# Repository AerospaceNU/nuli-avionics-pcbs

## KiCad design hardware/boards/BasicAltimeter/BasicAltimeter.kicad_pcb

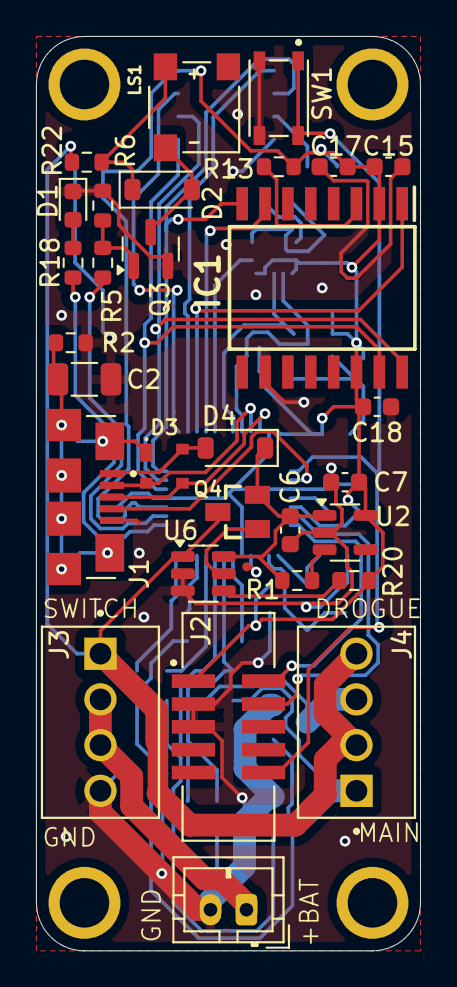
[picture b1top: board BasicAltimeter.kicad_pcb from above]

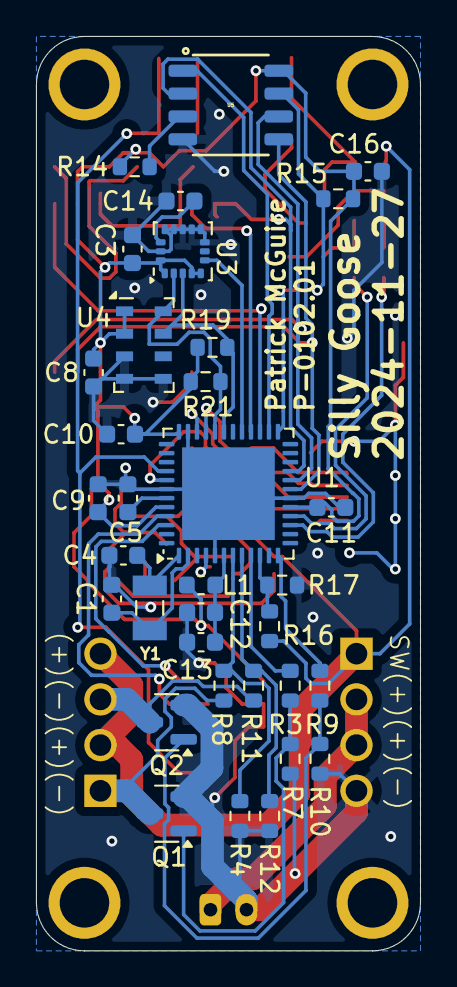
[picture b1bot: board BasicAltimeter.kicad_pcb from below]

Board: 2 copper layers, 21.3 x 50.8 mm, 69 parts (34 on the bottom side), 49 nets.

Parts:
C1, C4: 22pF; C_0603_1608Metric
C2: 4.7nF; C_1206_3216Metric
C3, C5, C8, C10, C11, C13, C14, C15, C18: 0.1uF; C_0603_1608Metric
C6, C7, C16: 10uF; C_0603_1608Metric
C9, C17: 1uF; C_0603_1608Metric
C12: 4.7uF; C_0603_1608Metric
D1: LED; LED_0603_1608Metric
D2, D4: D_Schottky; D_SOD-123
D3: PRTR5V0U2X_215; SOT143B
H1, H2, H3, H4: MountingHole; FixedMountingHole_2.5mm_Pad
IC1: S25FL512SAGMFV010; SOIC127P1030X265-16N
J1: ZX62-AB-5PA_31_; HIROSE_ZX62-AB-5PA_31_
J2: 20021521-00010T1LF; AMPHENOL_20021521-00010T1LF
J3, J4: Conn_01x04; TE_282834-4
J5: Conn_01x02; JST_PH_B2B-PH-K_1x02_P2.00mm_Vertical
L1: BLM18PG471SN1D; L_0603_1608Metric
LS1: CMT-0525-75-SMT-TR; XDCR_CMT-0525-75-SMT-TR
Q1, Q2, Q3: IRLML6244; SOT-23
Q4: FDN306P; SSOT-3
R1, R13: 100k; R_0603_1608Metric
R2, R20: 1M; R_0603_1608Metric
R3, R5, R9: 2k; R_0603_1608Metric
R4, R6, R7, R8, R10, R11, R12, R14, R15, R16, R17, R19, R21: 10k; R_0603_1608Metric
R18: 270; R_0603_1608Metric
R22: 50; R_0603_1608Metric
SW1: PTS810_SJM_250_SMTR_LFS; SW_PTS810_SJM_250_SMTR_LFS
TP12: TestPoint; TestPoint_Pad_D0.5mm
U1: ATSAMD21G18A-M; QFN-48-1EP_7x7mm_P0.5mm_EP5.15x5.15mm
U2: AP2112K-3.3; SOT-23-5
U3: ICM-20602; LGA-16_3x3mm_P0.5mm_LayoutBorder3x5y
U4: MS5607-02BA; LGA-8_3x5mm_P1.25mm
U5: MB85RS64V; SOIC127P600X155-8_R159_68_374R15
U6: LTC4412xS6; TSOT-23-6
Y1: ABS07-32.768KHZ-T; XTAL_ABS07-32.768KHZ-T

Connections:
+3.3V: C3.2, C5.2, C7.1, C8.2, C10.2, C11.2, C15.1, C16.2, C17.1, C18.2, IC1.2 (VCC), IC1.14 (VIO/RFU), J2.1, L1.1, R13.2, R14.1, R15.1, R19.1, R20.2, R21.1, U1.17 (VDDIO), U1.36 (VDDIO), U1.44 (VDDIN), U2.5 (VOUT), U3.1 (VDDIO), U3.4 (SAO/SD0), U3.5 (~CS), U3.16 (VDD), U4.1 (VDD), U4.2 (PS), U5.8 (VCC)
+BATT: J3.1, J4.2, J4.4, Q4.3, R16.1, R22.2, U6.1 (VIN)
/Connectors/D+: D3.3, J1.3 (D+), U1.34 (PA25)
/Connectors/D-: D3.2, J1.2 (D-), U1.33 (PA24)
/Connectors/DROGUE_CHANNEL: J4.3, Q2.3 (D), R11.2
/Connectors/MAIN_CHANNEL: J4.1, Q1.3 (D), R8.2
/Connectors/RESET: J2.10, SW1.1, SW1.2, U1.40 (~RESET)
/Connectors/SWCLK: J2.4, U1.45 (PA30)
/Connectors/SWDIO: J2.2, U1.46 (PA31)
/Connectors/USB_HOST: J1.4 (ID), U1.41 (PA28)
/Connectors/VUSB: D3.4, D4.2 (A), J1.1 (VCC)
/MCU/A1: R4.2, R8.1, U1.7 (PB08)
/MCU/A2: R11.1, R12.2, U1.8 (PB09)
/MCU/A3: R3.1, U1.9 (PA04)
/MCU/A4: R16.2, R17.1, U1.10 (PA05)
/MCU/AREF: TP12.1, U1.4 (PA03)
/MCU/D0_RX: R5.1, U1.16 (PA11)
/MCU/D1_TX: R18.1, U1.15 (PA10)
/MCU/D6: U1.29 (PA20), U3.6 (INT)
/MCU/D9: R9.1, U1.12 (PA07)
/MCU/D10: IC1.1 (HOLD#/IO3), U1.27 (PA18)
/MCU/D11: R15.2, U1.25 (PA16), U5.7 (~HOLD)
/MCU/D12: IC1.7 (CS#), U1.28 (PA19)
/MCU/D13: U1.26 (PA17), U5.1 (~CS)
/MCU/MISO: IC1.8 (SO/IO1), U1.21 (PA12), U5.2 (MISO)
/MCU/MOSI: IC1.15 (SI/IO0), U1.19 (PB10), U5.5 (MOSI)
/MCU/SCK: IC1.16 (SCK), U1.20 (PB11), U5.6 (SCK)
/MCU/SCL: R21.2, U1.32 (PA23), U3.2 (SCL/SPC), U4.8 (SCLK)
/MCU/SDA: R19.2, U1.31 (PA22), U3.3 (SDA/SDI), U4.7 (SDI/SDA)
/Power/STATUS: R20.1, U6.4 (STAT)
/Power/VChosen: C6.1, D4.1 (K), Q4.2, R1.1, U2.1 (VIN), U6.6 (SENSE)
/Status/BUZ_GATE: Q3.1 (G), R5.2, R6.2
GND: C1.2, C2.2, C3.1, C4.2, C5.1, C6.2, C7.2, C8.1, C9.2, C10.1, C11.1, C12.2, C13.2, C14.1, C15.2, C16.1, C17.2, C18.1, D1.1 (K), IC1.10 (VSS), J1.5 (GND), J2.3, J2.5, J3.4, J5.2, Q1.2 (S), Q2.2 (S), Q3.2 (S), R2.2, R4.1, R6.1, R7.1, R10.1, R12.1, R17.2, SW1.3, SW1.4, U1.5 (GNDANA), U1.18 (GND), U1.35 (GND), U1.42 (GND), U1.49 (EP), U2.2 (GND), U3.8 (FSYNC), U3.9 (GND), U3.10 (GND), U3.11 (GND), U3.12 (GND), U3.13 (GND), U3.15 (GND), U4.3 (GND), U4.4 (CSB), U4.5 (CSB), U5.4 (GND), U6.2 (GND), U6.3 (CTL)
unnamed: D1.2 (A), R18.2
unnamed: D2.2 (A), LS1.N, Q3.3 (D)
unnamed: D2.1 (K), LS1.P, R22.1
unnamed: IC1.3 (RESET#/RFU), R13.1
unnamed: J3.2, J3.3, J5.1
unnamed: Q1.1 (G), R3.2, R7.2
unnamed: Q2.1 (G), R9.2, R10.2
unnamed: C4.1, U1.1 (PA00), Y1.1
unnamed: C1.1, U1.2 (PA01), Y1.2
unnamed: C12.1, C13.1, L1.2, U1.6 (VDDANA)
unnamed: C9.1, U1.43 (VDDCORE)
unnamed: R1.2, U2.3 (EN)
unnamed: C14.2, U3.14 (REGOUT)
unnamed: R14.2, U5.3 (~WP)
unnamed: Q4.1, U6.5 (GATE)
SHIELD: C2.1, D3.1, J1.S1 (SHIELD), J1.S2 (SHIELD), J1.S3 (SHIELD), J1.S4 (SHIELD), J1.S5 (SHIELD), J1.S6 (SHIELD), R2.1

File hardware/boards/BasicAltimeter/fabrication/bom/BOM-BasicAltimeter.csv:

Comment,Designator,Footprint,LCSC
PRTR5V0U2X_215,D3,SOT143B,C12333
MB85RS64V,U5,SOIC127P600X155-8_R159_68_374R15,C126731
ABS07-32.768KHZ-T,Y1,XTAL_ABS07-32.768KHZ-T,C130253
Conn_01x02,J5,JST_PH_B2B-PH-K_1x02_P2.00mm_Vertical,C131337
IRLML6244,"Q1,Q2,Q3",SOT-23,C143946
0.1uF,"C10,C11,C13,C14,C15,C18,C3,C5,C8",C_0603_1608Metric,C14663
FDN306P,Q4,SSOT-3,C154510
1uF,"C17,C9",C_0603_1608Metric,C15849
22pF,"C1,C4",C_0603_1608Metric,C1653
4.7uF,C12,C_0603_1608Metric,C19666
10uF,"C16,C6,C7",C_0603_1608Metric,C19702
PTS810_SJM_250_SMTR_LFS,SW1,SW_PTS810_SJM_250_SMTR_LFS,C221895
S25FL512SAGMFV010,IC1,SOIC127P1030X265-16N,C22399738
1M,"R2,R20",R_0603_1608Metric,C22935
270,R18,R_0603_1608Metric,C22966
2k,"R3,R5,R9",R_0603_1608Metric,C22975
100k,"R1,R13",R_0603_1608Metric,C25803
10k,"R10,R11,R12,R14,R15,R16,R17,R19,R21,R4,R6,R7,R8",R_0603_1608Metric,C25804
ZX62-AB-5PA_31_,J1,HIROSE_ZX62-AB-5PA_31_,C2692071
20021521-00010T1LF,J2,AMPHENOL_20021521-00010T1LF,C2972785
LED,D1,LED_0603_1608Metric,C3000897
CMT-0525-75-SMT-TR,LS1,XDCR_CMT-0525-75-SMT-TR,C3812222
Conn_01x04,"J3,J4",TE_282834-4,C3820029
AP2112K-3.3,U2,SOT-23-5,C51118
LTC4412xS6,U6,TSOT-23-6,C514442
D_Schottky,"D2,D4",D_SOD-123,C82544
50,R22,R_0603_1608Metric,C849792
4.7nF,C2,C_1206_3216Metric,C9192
ATSAMD21G18A-M,U1,QFN-48-1EP_7x7mm_P0.5mm_EP5.15x5.15mm,C966903
MS5607-02BA,U4,LGA-8_3x5mm_P1.25mm,C97627
ICM-20602,U3,LGA-16_3x3mm_P0.5mm_LayoutBorder3x5y,C97633
BLM18PG471SN1D,L1,L_0603_1608Metric,C97853

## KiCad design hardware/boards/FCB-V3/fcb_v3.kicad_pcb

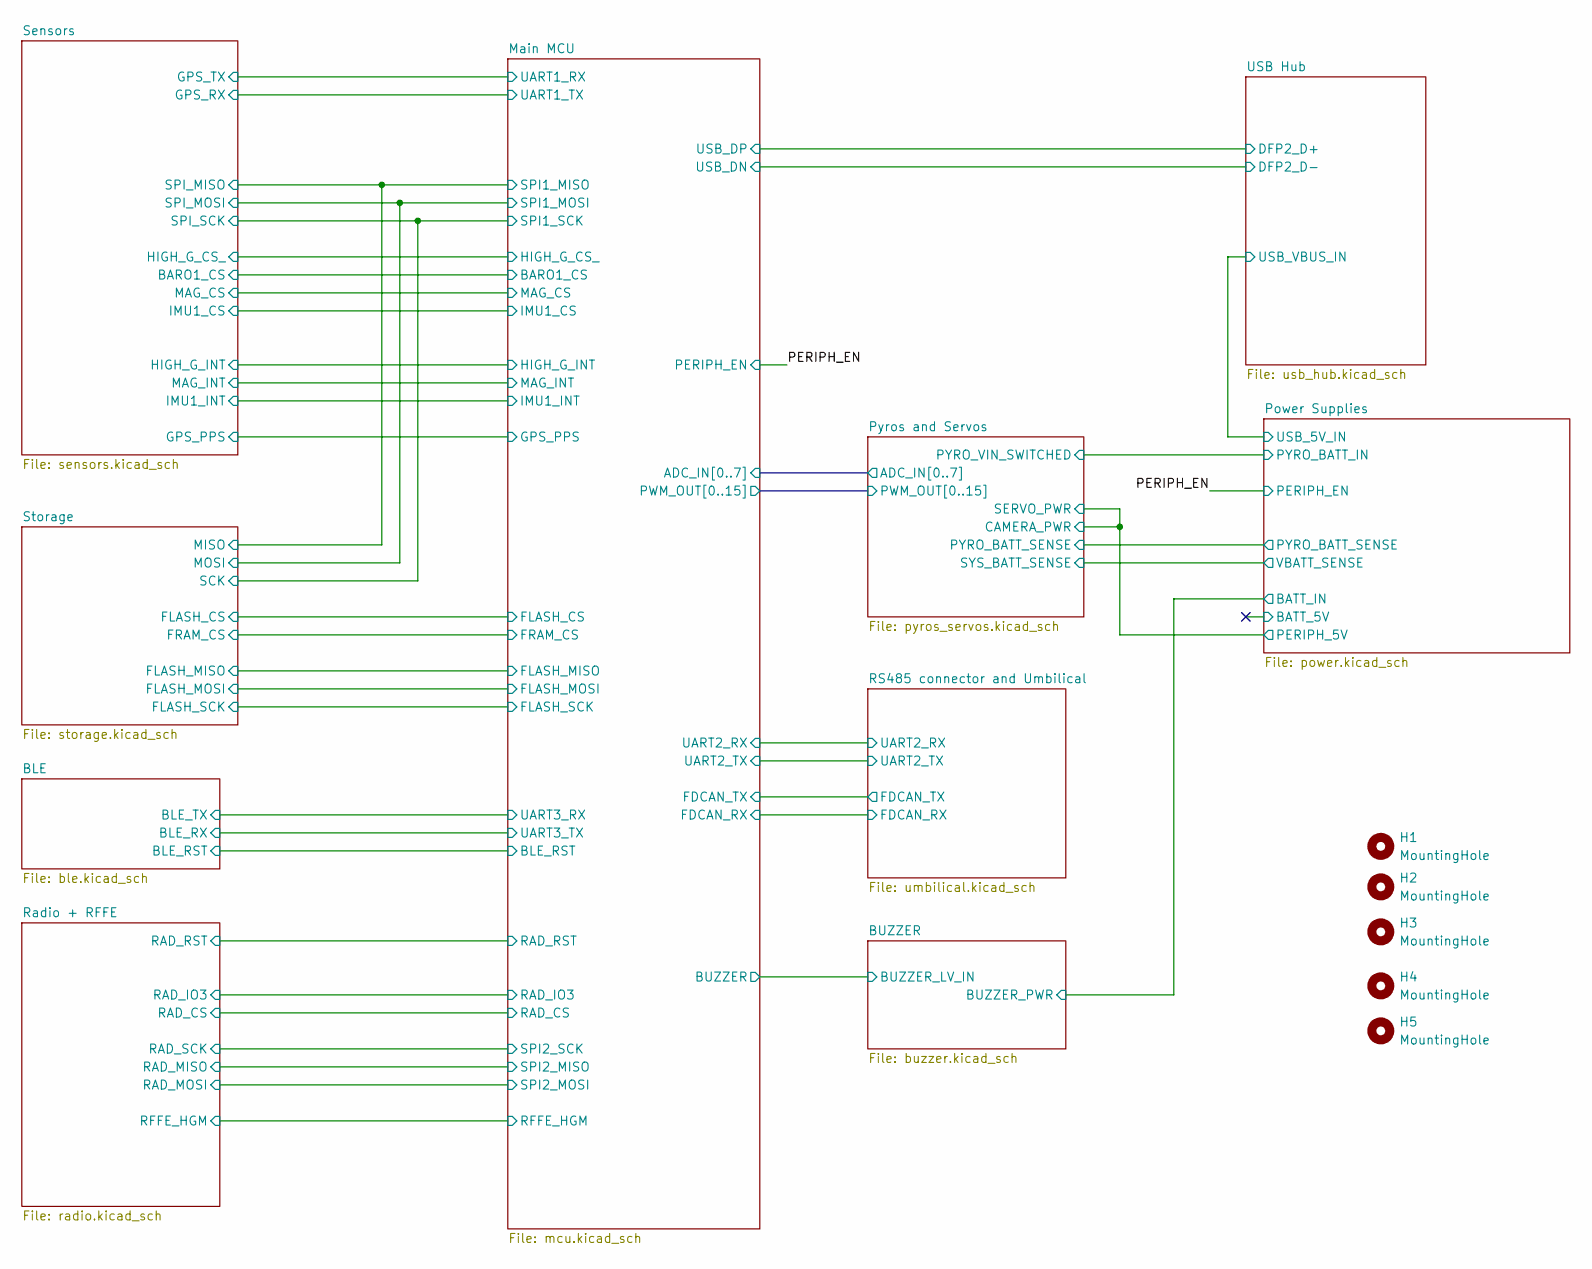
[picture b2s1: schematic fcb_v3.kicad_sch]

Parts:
H1, H2, H3, H4, H5: MountingHole; MountingHole_2.2mm_M2

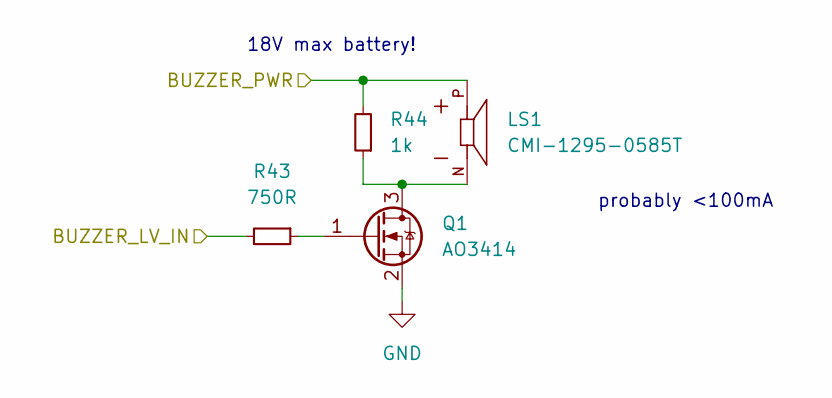
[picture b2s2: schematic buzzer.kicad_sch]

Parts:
LS1: CMI-1295-0585T; CUI_CMI-1295-0585T; PARTREV N/A
Q1: AO3414; SOT-23
R43: 750R; R_0402_1005Metric; LCSC C25130
R44: 1k; R_0402_1005Metric

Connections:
/BUZZER/BUZZER_LV_IN: R43.2; also elsewhere on the board
/Power Supplies/BATT_SYS_IN: LS1.P, R44.2; also elsewhere on the board
GND: Q1.2 (S); also elsewhere on the board
unnamed: LS1.N, Q1.3 (D), R44.1
unnamed: Q1.1 (G), R43.1

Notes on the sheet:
probably <100mA
18V max battery!

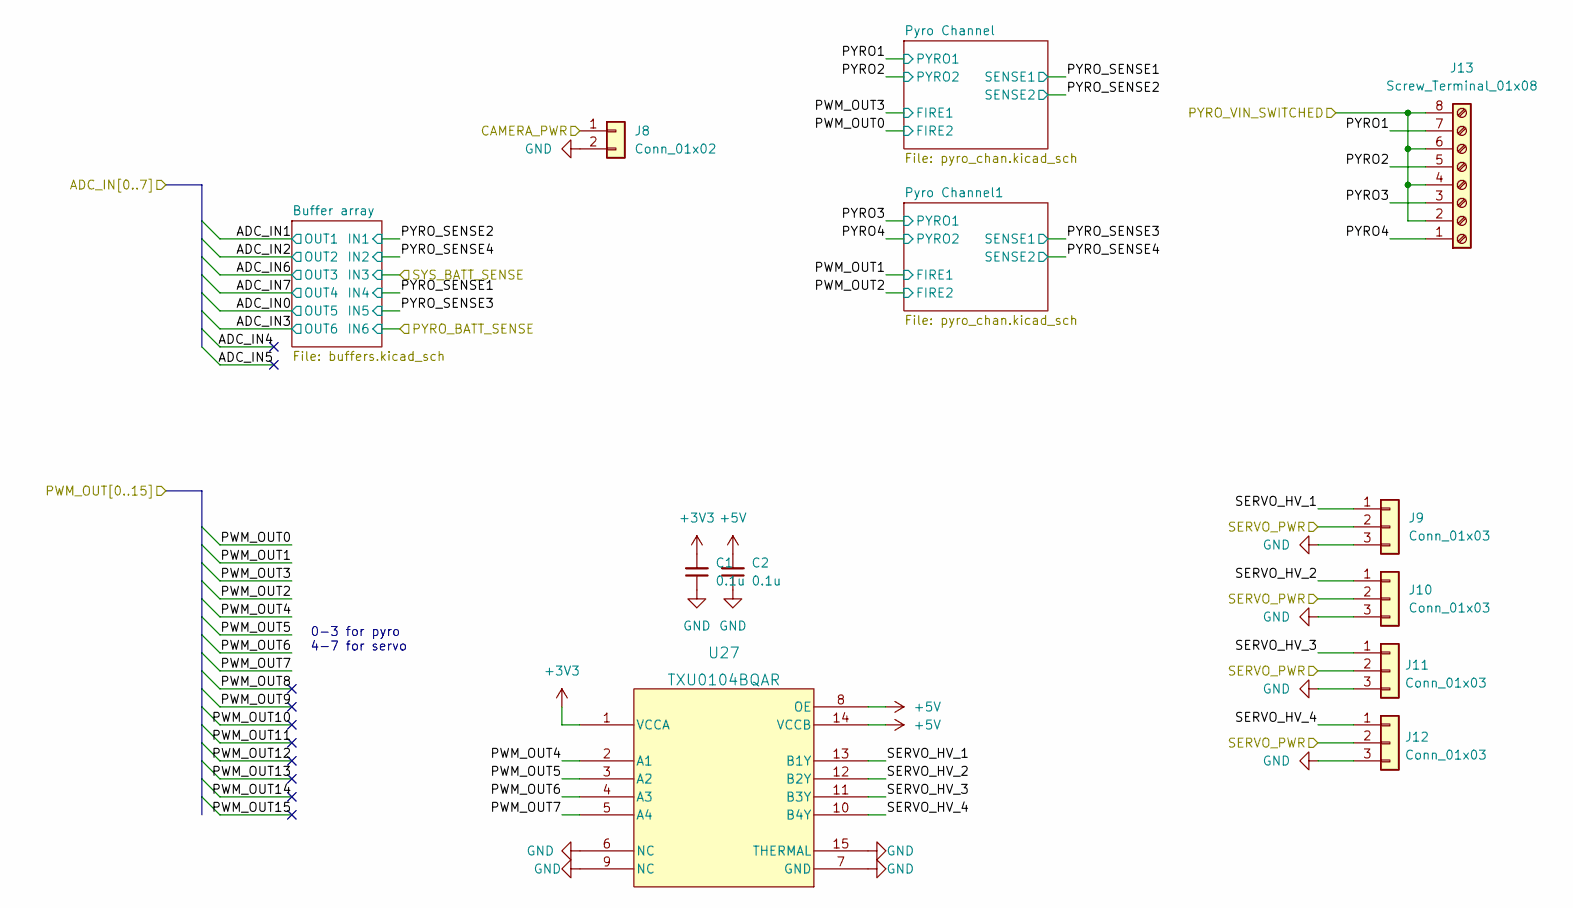
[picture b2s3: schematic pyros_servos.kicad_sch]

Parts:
C1, C2: 0.1u; C_0402_1005Metric
J8: Conn_01x02; JST_XH_B2B-XH-A_1x02_P2.50mm_Vertical
J9, J10, J11, J12: Conn_01x03; JST_PH_B3B-PH-SM4-TB_1x03-1MP_P2.00mm_Vertical
J13: Screw_Terminal_01x08; TerminalBlock_TE_282834-8_1x08_P2.54mm_Horizontal
U27: TXU0104BQAR; U_TXU0104_TEX

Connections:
+3V3: C1.2, U27.1 (VCCA); also elsewhere on the board
+5V: C2.2, U27.8 (OE), U27.14 (VCCB); also elsewhere on the board
/Main MCU/PWM_OUT4: U27.2 (A1); also elsewhere on the board
/Main MCU/PWM_OUT5: U27.3 (A2); also elsewhere on the board
/Main MCU/PWM_OUT6: U27.4 (A3); also elsewhere on the board
/Main MCU/PWM_OUT7: U27.5 (A4); also elsewhere on the board
/Power Supplies/BATT_PYRO_IN: J13.2, J13.4, J13.6, J13.8; also elsewhere on the board
/Power Supplies/PERIPH_5V: J8.1, J9.2, J10.2, J11.2, J12.2; also elsewhere on the board
/Pyros and Servos/PYRO1: J13.7; also elsewhere on the board
/Pyros and Servos/PYRO2: J13.5; also elsewhere on the board
/Pyros and Servos/PYRO3: J13.3; also elsewhere on the board
/Pyros and Servos/PYRO4: J13.1; also elsewhere on the board
/Pyros and Servos/SERVO_HV_1: J9.1, U27.13 (B1Y)
/Pyros and Servos/SERVO_HV_2: J10.1, U27.12 (B2Y)
/Pyros and Servos/SERVO_HV_3: J11.1, U27.11 (B3Y)
/Pyros and Servos/SERVO_HV_4: J12.1, U27.10 (B4Y)
GND: C1.1, C2.1, J8.2, J9.3, J10.3, J11.3, J12.3, U27.6 (NC), U27.7 (GND), U27.9 (NC), U27.15 (THERMAL); also elsewhere on the board

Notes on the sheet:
0-3 for pyro 4-7 for servo

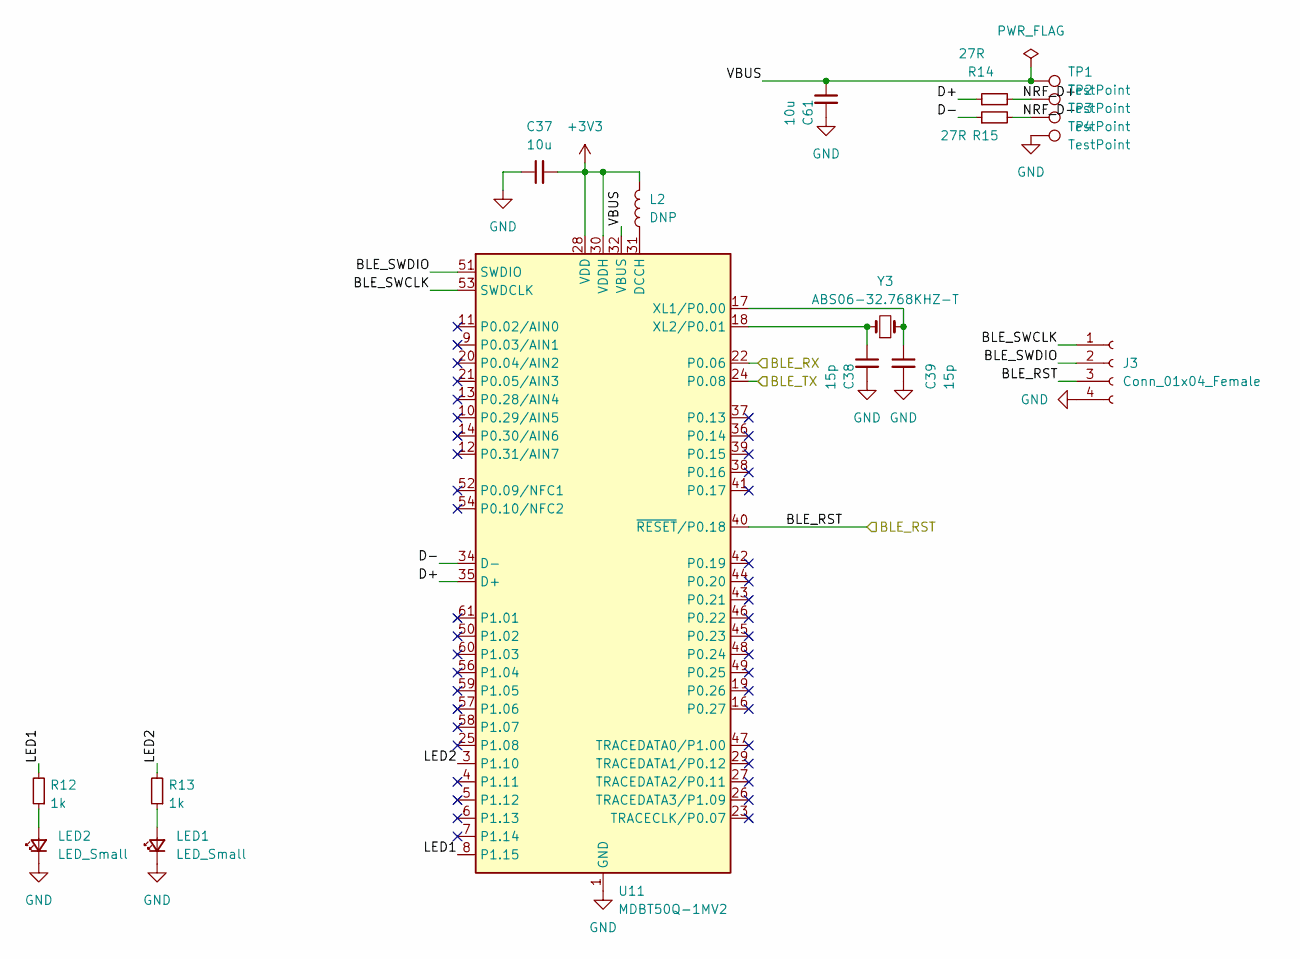
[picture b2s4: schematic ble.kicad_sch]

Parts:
C37: 10u; C_0603_1608Metric
C38, C39: 15p; C_0402_1005Metric
C61: 10u; C_0402_1005Metric
J3: Conn_01x04_Female; PinSocket_1x04_P2.00mm_Vertical
L2: DNP; L_0603_1608Metric
LED1, LED2: LED_Small; LED_0603_1608Metric
R12, R13: 1k; R_0402_1005Metric
R14, R15: 27R; R_0402_1005Metric
TP1, TP2, TP3, TP4: TestPoint; TestPoint_Pad_D1.0mm
U11: MDBT50Q-1MV2; Raytac_MDBT50Q
Y3: ABS06-32.768KHZ-T; Crystal_SMD_3215-2Pin_3.2x1.5mm; LCSC C32346

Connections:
+3V3: C37.2, L2.2, U11.28 (VDD), U11.30 (VDDH); also elsewhere on the board
/BLE/BLE_RST: J3.3, U11.40 (~RESET/P0.18); also elsewhere on the board
/BLE/BLE_RX: U11.22 (P0.06); also elsewhere on the board
/BLE/BLE_SWCLK: J3.1, U11.53 (SWDCLK)
/BLE/BLE_SWDIO: J3.2, U11.51 (SWDIO)
/BLE/BLE_TX: U11.24 (P0.08); also elsewhere on the board
/BLE/D+: R14.1, U11.35 (D+)
/BLE/D-: R15.1, U11.34 (D-)
/BLE/LED1: R12.2, U11.8 (P1.15)
/BLE/LED2: R13.2, U11.3 (P1.10)
/BLE/NRF_D+: R14.2, TP2.1
/BLE/NRF_D-: R15.2, TP3.1
/BLE/VBUS: C61.1, TP1.1, U11.32 (VBUS)
GND: C37.1, C38.2, C39.2, C61.2, J3.4, LED1.1 (K), LED2.1 (K), TP4.1, U11.1 (GND), U11.2 (GND), U11.15 (GND), U11.33 (GND), U11.55 (GND); also elsewhere on the board
unnamed: LED1.2 (A), R13.1
unnamed: LED2.2 (A), R12.1
unnamed: L2.1, U11.31 (DCCH)
unnamed: C39.1, U11.17 (XL1/P0.00), Y3.2
unnamed: C38.1, U11.18 (XL2/P0.01), Y3.1

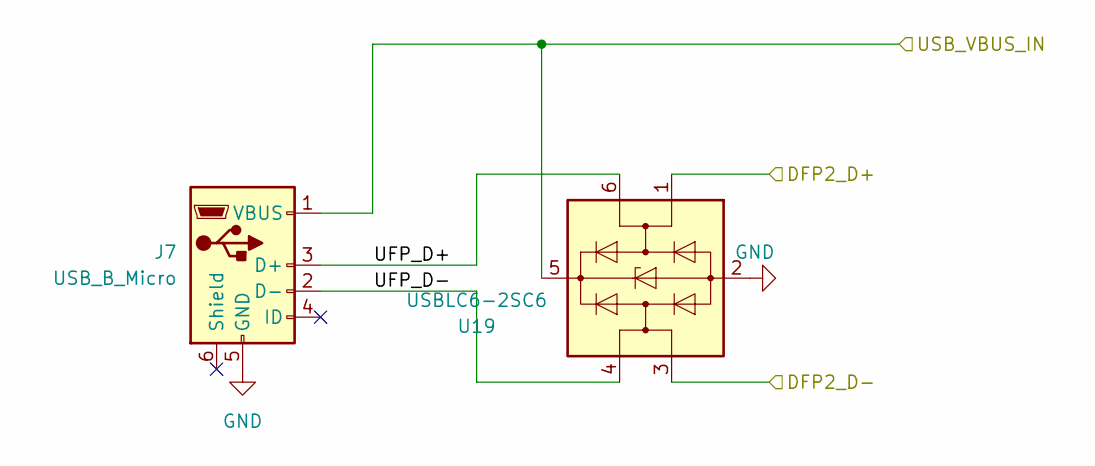
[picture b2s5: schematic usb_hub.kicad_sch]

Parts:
J7: USB_B_Micro; USB_Micro-B_Wuerth_629105150521
U19: USBLC6-2SC6; SOT-23-6

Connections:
/Main MCU/USB_DN: U19.3 (I/O2); also elsewhere on the board
/Main MCU/USB_DP: U19.1 (I/O1); also elsewhere on the board
/Power Supplies/USB_5V_IN: J7.1 (VBUS), U19.5 (VBUS); also elsewhere on the board
/USB Hub/UFP_D+: J7.3 (D+), U19.6 (I/O1)
/USB Hub/UFP_D-: J7.2 (D-), U19.4 (I/O2)
GND: J7.5 (GND), U19.2 (GND); also elsewhere on the board

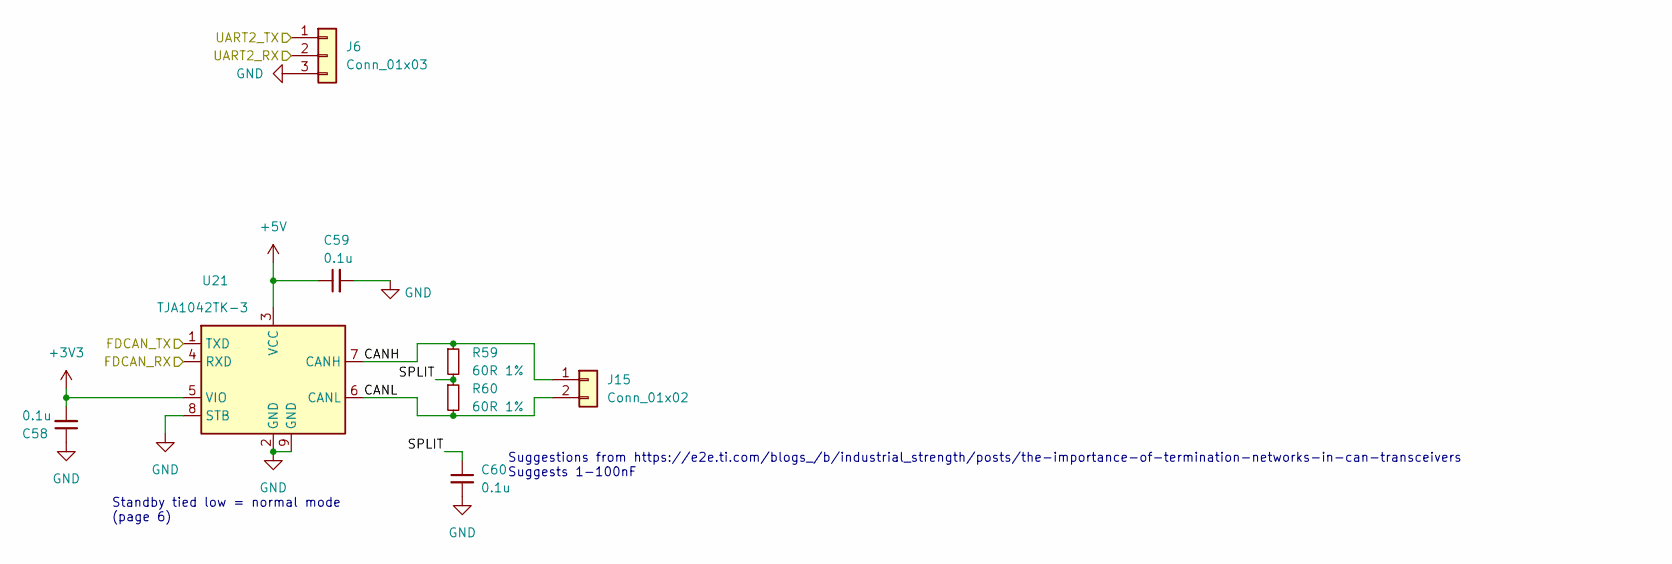
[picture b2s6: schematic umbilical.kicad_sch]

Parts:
C58, C59, C60: 0.1u; C_0402_1005Metric
J6: Conn_01x03; JST_PH_B3B-PH-SM4-TB_1x03-1MP_P2.00mm_Vertical
J15: Conn_01x02; JST_PH_B2B-PH-SM4-TB_1x02-1MP_P2.00mm_Vertical
R59, R60: 60R 1%; R_0402_1005Metric
U21: TJA1042TK-3; DFN-8-1EP_3x3mm_P0.65mm_EP1.55x2.4mm

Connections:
+3V3: C58.2, U21.5 (VIO); also elsewhere on the board
+5V: C59.1, U21.3 (VCC); also elsewhere on the board
/Main MCU/FDCAN_RX: U21.4 (RXD); also elsewhere on the board
/Main MCU/FDCAN_TX: U21.1 (TXD); also elsewhere on the board
/Main MCU/UART2_RX: J6.2; also elsewhere on the board
/Main MCU/UART2_TX: J6.1; also elsewhere on the board
/RS485 connector and Umbilical/CANH: J15.1, R59.1, U21.7 (CANH)
/RS485 connector and Umbilical/CANL: J15.2, R60.2, U21.6 (CANL)
/RS485 connector and Umbilical/SPLIT: C60.1, R59.2, R60.1
GND: C58.1, C59.2, C60.2, J6.3, U21.2 (GND), U21.8 (STB), U21.9 (GND); also elsewhere on the board

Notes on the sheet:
Suggestions from https://e2e.ti.com/blogs_/b/industrial_strength/posts/the-importance-of-termination-networks-in-can-transceivers Suggests 1-100nF
Standby tied low = normal mode (page 6)

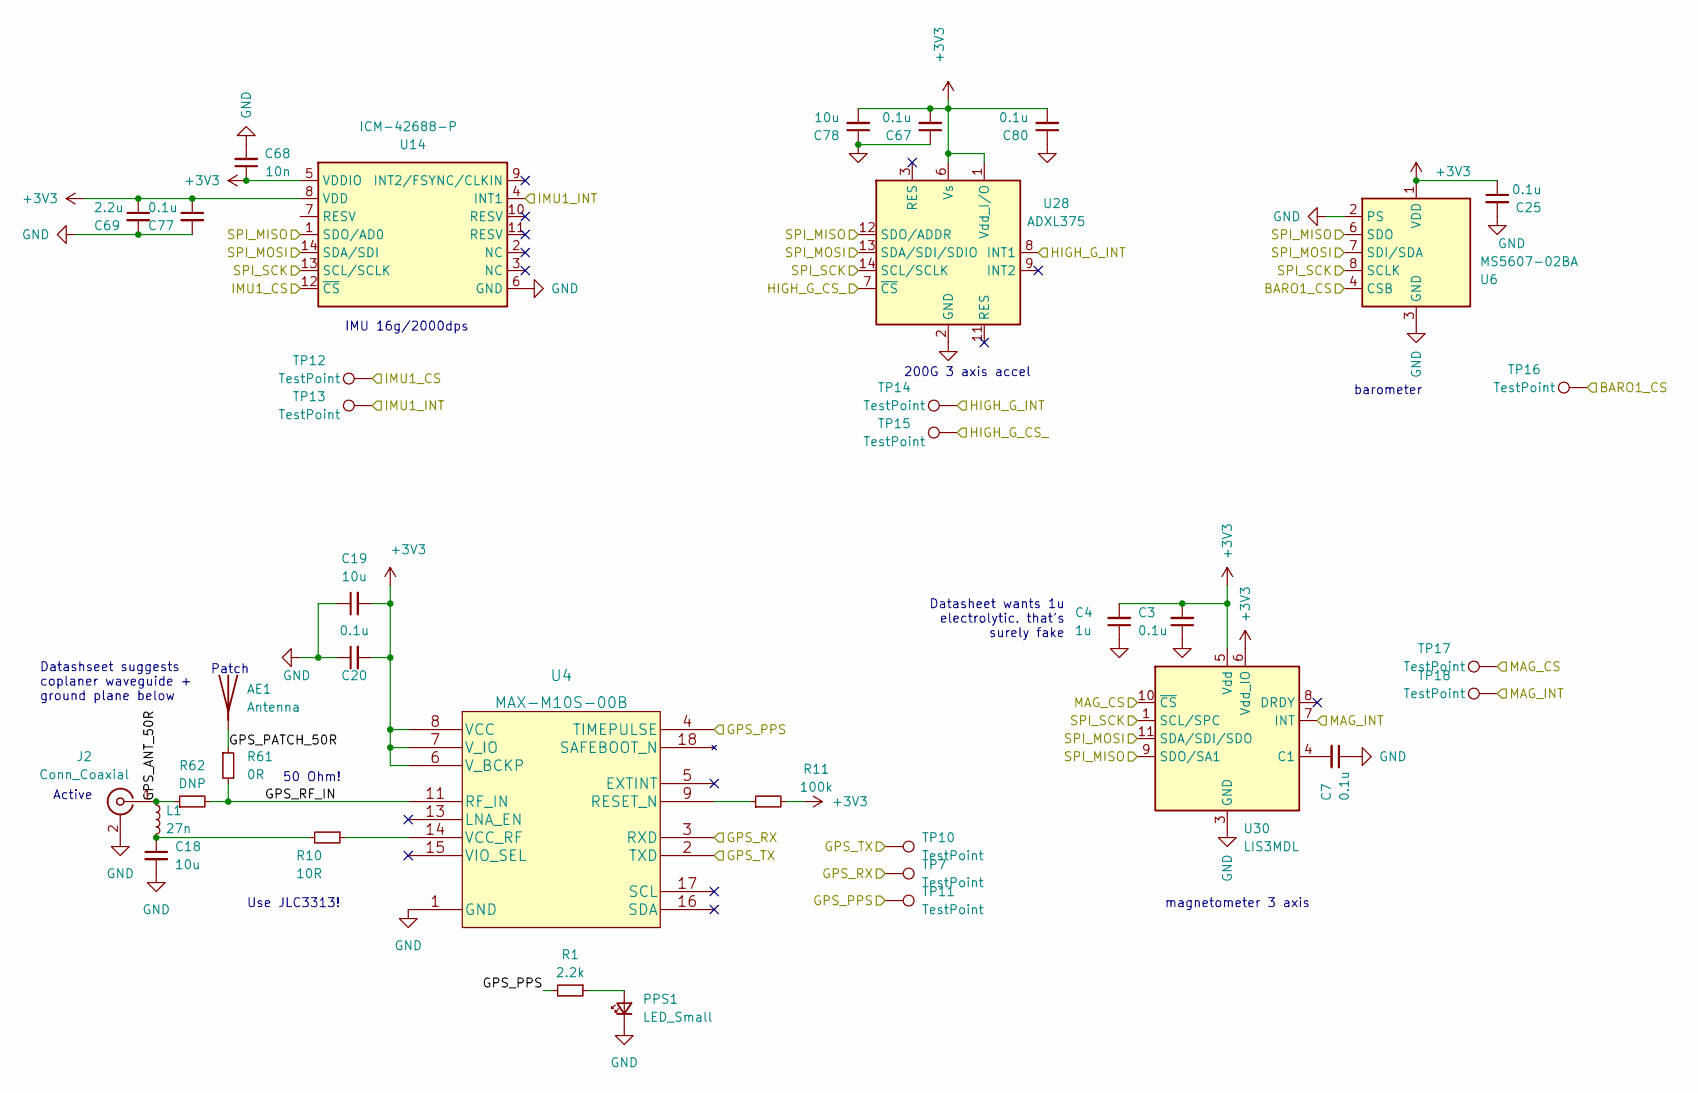
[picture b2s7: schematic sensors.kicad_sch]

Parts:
AE1: Antenna; CGGBP.18.4.A.02
C3, C7, C20, C25, C67, C77, C80: 0.1u; C_0402_1005Metric
C4: 1u; C_0402_1005Metric
C18, C19, C78: 10u; C_0603_1608Metric
C68: 10n; C_0402_1005Metric
C69: 2.2u; C_0603_1608Metric
J2: Conn_Coaxial; SMA_Molex_73251-1153_EdgeMount_Horizontal
L1: 27n; L_0402_1005Metric; LCSC C2041663
PPS1: LED_Small; LED_0603_1608Metric
R1: 2.2k; R_0402_1005Metric
R10: 10R; R_0402_1005Metric; LCSC C25077
R11: 100k; R_0402_1005Metric
R61: 0R; R_0603_1608Metric; LCSC C21189
R62: DNP; R_0603_1608Metric
TP7, TP10, TP11, TP12, TP13, TP14, TP15, TP16, TP17, TP18: TestPoint; TestPoint_Pad_D1.0mm
U4: MAX-M10S-00B; XCVR_MAX-M8C-0-10
U6: MS5607-02BA; LGA-8_3x5mm_P1.25mm
U14: ICM-42688-P; LGA-14_3x2.5mm_P0.5mm_LayoutBorder3x4y
U28: ADXL375; LGA-14_3x5mm_P0.8mm_LayoutBorder1x6y
U30: LIS3MDL; LGA-12_2x2mm_P0.5mm

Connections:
+3V3: C3.2, C4.2, C19.2, C20.2, C25.1, C67.2, C68.1, C69.1, C77.1, C78.2, C80.2, R11.2, U4.6 (V_BCKP), U4.7 (V_IO), U4.8 (VCC), U6.1 (VDD), U14.5 (VDDIO), U14.8 (VDD), U28.1 (Vdd_I/O), U28.6 (Vs), U30.5 (Vdd), U30.6 (Vdd_IO); also elsewhere on the board
/Main MCU/BARO1_CS: TP16.1, U6.4 (CSB), U6.5 (CSB); also elsewhere on the board
/Main MCU/HIGH_G_CS_: TP15.1, U28.7 (~CS); also elsewhere on the board
/Main MCU/HIGH_G_INT: TP14.1, U28.8 (INT1); also elsewhere on the board
/Main MCU/IMU1_CS: TP12.1, U14.12 (~CS); also elsewhere on the board
/Main MCU/IMU1_INT: TP13.1, U14.4 (INT1); also elsewhere on the board
/Main MCU/MAG_CS: TP17.1, U30.10 (~CS); also elsewhere on the board
/Main MCU/MAG_INT: TP18.1, U30.7 (INT); also elsewhere on the board
/Main MCU/SPI1_MISO: U6.6 (SDO), U14.1 (SDO/AD0), U28.12 (SDO/ADDR), U30.9 (SDO/SA1); also elsewhere on the board
/Main MCU/SPI1_MOSI: U6.7 (SDI/SDA), U14.14 (SDA/SDI), U28.13 (SDA/SDI/SDIO), U30.11 (SDA/SDI/SDO); also elsewhere on the board
/Main MCU/SPI1_SCK: U6.8 (SCLK), U14.13 (SCL/SCLK), U28.14 (SCL/SCLK), U30.1 (SCL/SPC); also elsewhere on the board
/Main MCU/UART1_RX: TP10.1, U4.2 (TXD); also elsewhere on the board
/Main MCU/UART1_TX: TP7.1, U4.3 (RXD); also elsewhere on the board
/Sensors/GPS_ANT_50R: J2.1 (In), L1.1, R62.1
/Sensors/GPS_PATCH_50R: AE1.1 (A), R61.1
/Sensors/GPS_PPS: R1.2, TP11.1, U4.4 (TIMEPULSE); also elsewhere on the board
/Sensors/GPS_RF_IN: R61.2, R62.2, U4.11 (RF_IN)
GND: C3.1, C4.1, C7.1, C18.2, C19.1, C20.1, C25.2, C67.1, C68.2, C69.2, C77.2, C78.1, C80.1, J2.2 (Ext), PPS1.1 (K), U4.1 (GND), U4.10 (GND), U4.12 (GND), U6.2 (PS), U6.3 (GND), U14.6 (GND), U28.2 (GND), U28.4 (GND), U28.5 (GND), U30.2 (GND), U30.3 (GND), U30.12 (GND); also elsewhere on the board
unnamed: C18.1, L1.2, R10.2
unnamed: PPS1.2 (A), R1.1
unnamed: R11.1, U4.9 (RESET_N)
unnamed: R10.1, U4.14 (VCC_RF)
unnamed: C7.2, U30.4 (C1)

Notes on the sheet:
magnetometer 3 axis
Use JLC3313!
Datashseet suggests coplaner waveguide + ground plane below
50 Ohm!
Active
IMU 16g/2000dps
Patch
Datasheet wants 1u electrolytic. that's surely fake
200G 3 axis accel
barometer

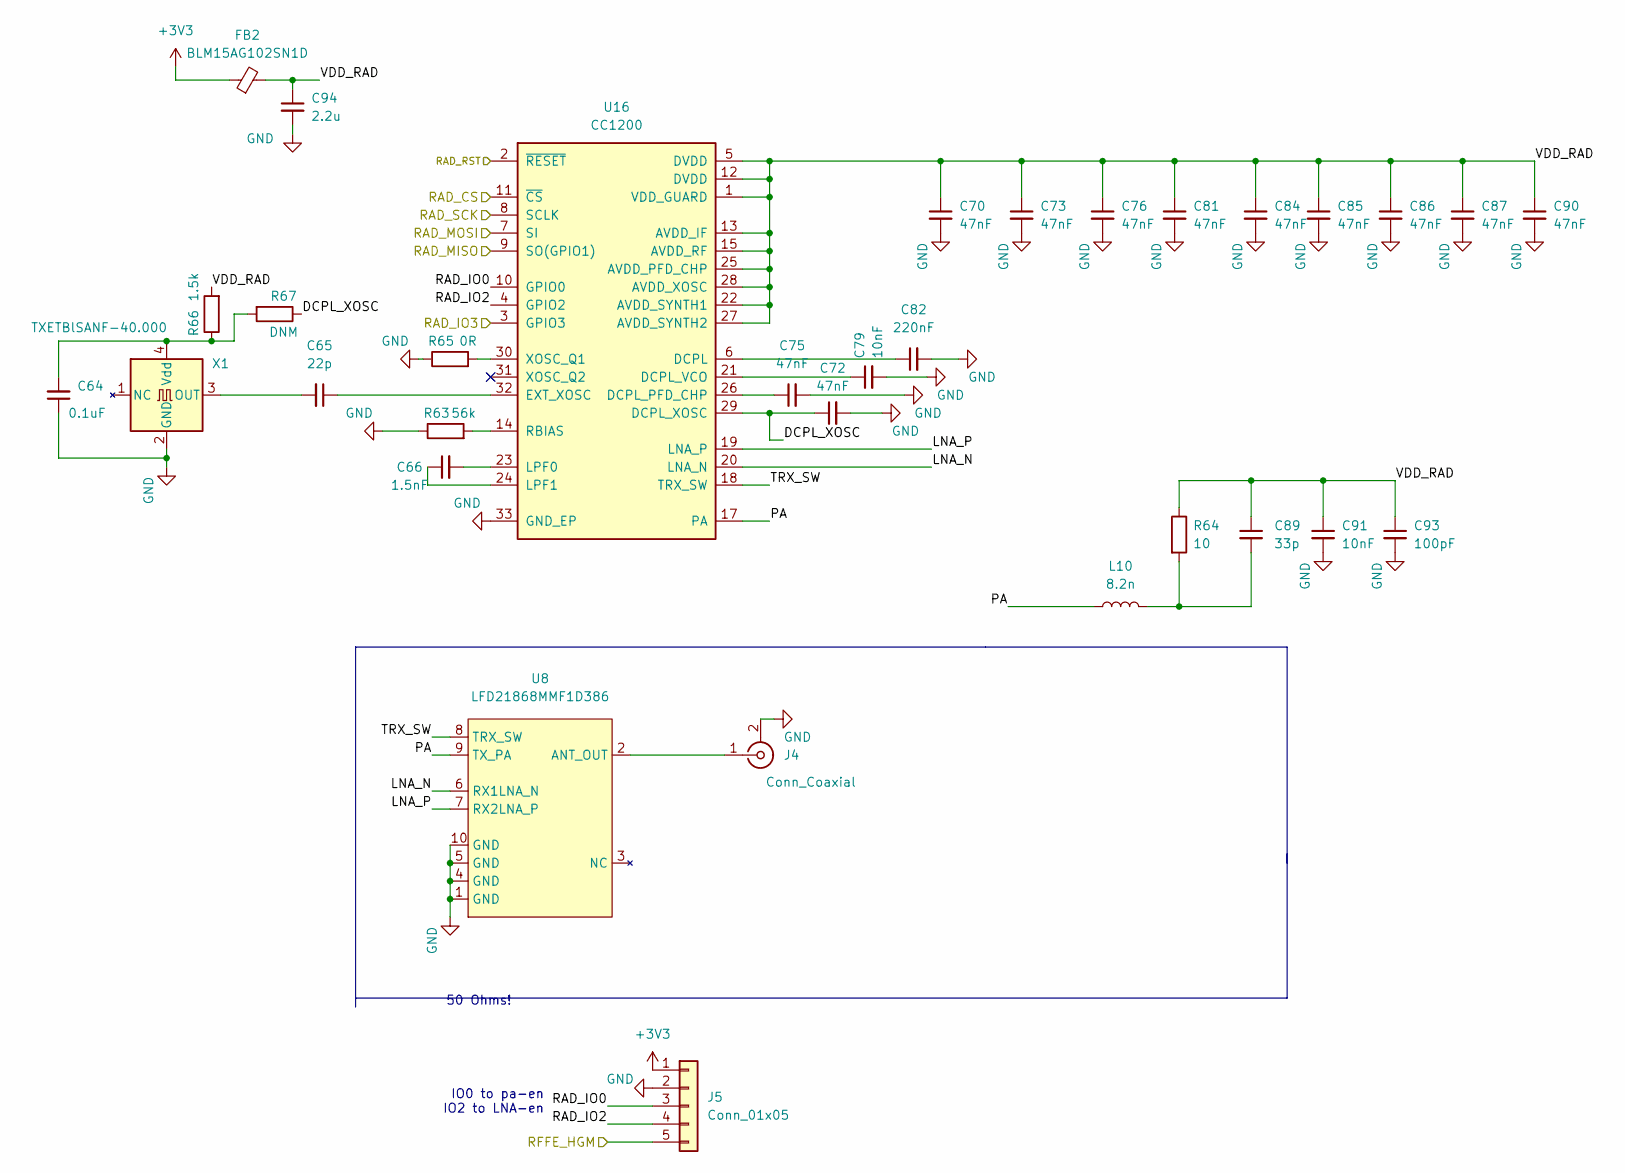
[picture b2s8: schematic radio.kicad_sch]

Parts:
C64: 0.1uF; C_0402_1005Metric
C65: 22p; C_0402_1005Metric
C66: 1.5nF; C_0402_1005Metric
C70, C72, C73, C75, C76, C81, C84, C85, C86, C87, C90: 47nF; C_0402_1005Metric; LCSC C913545
C79, C91: 10nF; C_0402_1005Metric
C82: 220nF; C_0402_1005Metric
C89: 33p; C_0402_1005Metric
C93: 100pF; C_0402_1005Metric
C94: 2.2u; C_0402_1005Metric
FB2: BLM15AG102SN1D; L_0402_1005Metric
J4: Conn_Coaxial; SMA_Molex_73251-1153_EdgeMount_Horizontal
J5: Conn_01x05; PinHeader_1x05_P2.00mm_Vertical
L10: 8.2n; L_0402_1005Metric
R63: 56k; R_0402_1005Metric
R64: 10; R_0402_1005Metric
R65: 0R; R_0402_1005Metric
R66: 1.5k; R_0402_1005Metric
R67: DNM; R_0402_1005Metric
U8: LFD21868MMF1D386; LFD21868MMF1D386_MUR
U16: CC1200; QFN-32-1EP_5x5mm_P0.5mm_EP3.45x3.45mm
X1: TXETBlSANF-40.000; Oscillator_SMD_TXC_7C-4Pin_5.0x3.2mm

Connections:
+3V3: FB2.1, J5.1; also elsewhere on the board
/Main MCU/RAD_CS: U16.11 (~CS); also elsewhere on the board
/Main MCU/RAD_IO3: U16.3 (GPIO3); also elsewhere on the board
/Main MCU/RAD_RST: U16.2 (~RESET); also elsewhere on the board
/Main MCU/RFFE_HGM: J5.5; also elsewhere on the board
/Main MCU/SPI2_MISO: U16.9 (SO(GPIO1)); also elsewhere on the board
/Main MCU/SPI2_MOSI: U16.7 (SI); also elsewhere on the board
/Main MCU/SPI2_SCK: U16.8 (SCLK); also elsewhere on the board
/Radio + RFFE/DCPL_XOSC: C72.1, R67.1, U16.29 (DCPL_XOSC)
/Radio + RFFE/LNA_N: U8.6 (RX1LNA_N), U16.20 (LNA_N)
/Radio + RFFE/LNA_P: U8.7 (RX2LNA_P), U16.19 (LNA_P)
/Radio + RFFE/PA: L10.1, U8.9 (TX_PA), U16.17 (PA)
/Radio + RFFE/RAD_IO0: J5.3, U16.10 (GPIO0)
/Radio + RFFE/RAD_IO2: J5.4, U16.4 (GPIO2)
/Radio + RFFE/TRX_SW: U8.8 (TRX_SW), U16.18 (TRX_SW)
/Radio + RFFE/VDD_RAD: C70.1, C73.1, C76.1, C81.1, C84.1, C85.1, C86.1, C87.1, C89.1, C90.1, C91.1, C93.1, C94.1, FB2.2, R64.1, R66.2, U16.1 (VDD_GUARD), U16.5 (DVDD), U16.12 (DVDD), U16.13 (AVDD_IF), U16.15 (AVDD_RF), U16.22 (AVDD_SYNTH1), U16.25 (AVDD_PFD_CHP), U16.27 (AVDD_SYNTH2), U16.28 (AVDD_XOSC)
GND: C64.1, C70.2, C72.2, C73.2, C75.2, C76.2, C79.2, C81.2, C82.2, C84.2, C85.2, C86.2, C87.2, C90.2, C91.2, C93.2, C94.2, J4.2 (Ext), J5.2, R63.1, R65.1, U8.1 (GND), U8.4 (GND), U8.5 (GND), U8.10 (GND), U16.33 (GND_EP), X1.2 (GND); also elsewhere on the board
unnamed: C89.2, L10.2, R64.2
unnamed: J4.1 (In), U8.2 (ANT_OUT)
unnamed: C82.1, U16.6 (DCPL)
unnamed: C75.1, U16.26 (DCPL_PFD_CHP)
unnamed: C79.1, U16.21 (DCPL_VCO)
unnamed: C65.1, U16.32 (EXT_XOSC)
unnamed: C66.2, U16.23 (LPF0)
unnamed: C66.1, U16.24 (LPF1)
unnamed: R63.2, U16.14 (RBIAS)
unnamed: R65.2, U16.30 (XOSC_Q1)
unnamed: C65.2, X1.3 (OUT)
unnamed: C64.2, R66.1, R67.2, X1.4 (Vdd)

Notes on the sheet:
50 Ohms!
IO0 to pa-en IO2 to LNA-en

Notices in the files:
parts and their libraries:
Copyright 2021 Accelerated Designs. All rights reserved.
